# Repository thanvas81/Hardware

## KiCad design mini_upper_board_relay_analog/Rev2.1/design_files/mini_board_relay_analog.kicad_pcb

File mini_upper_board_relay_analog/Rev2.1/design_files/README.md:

# LUX_Project

## Getting started

To make it easy for you to get started with GitLab, here's a list of recommended next steps.

Already a pro? Just edit this README.md and make it your own. Want to make it easy? [Use the template at the bottom](#editing-this-readme)!

## Add your files

- [ ] [Create](https://docs.gitlab.com/ee/user/project/repository/web_editor.html#create-a-file) or [upload](https://docs.gitlab.com/ee/user/project/repository/web_editor.html#upload-a-file) files
- [ ] [Add files using the command line](https://docs.gitlab.com/ee/gitlab-basics/add-file.html#add-a-file-using-the-command-line) or push an existing Git repository with the following command:

```
cd existing_repo
git remote add origin http://192.168.1.53/hardware/boards/lux_project.git
git branch -M main
git push -uf origin main
```

## Integrate with your tools

- [ ] [Set up project integrations](http://192.168.1.53/hardware/boards/lux_project/-/settings/integrations)

## Collaborate with your team

- [ ] [Invite team members and collaborators](https://docs.gitlab.com/ee/user/project/members/)
- [ ] [Create a new merge request](https://docs.gitlab.com/ee/user/project/merge_requests/creating_merge_requests.html)
- [ ] [Automatically close issues from merge requests](https://docs.gitlab.com/ee/user/project/issues/managing_issues.html#closing-issues-automatically)
- [ ] [Enable merge request approvals](https://docs.gitlab.com/ee/user/project/merge_requests/approvals/)
- [ ] [Set auto-merge](https://docs.gitlab.com/ee/user/project/merge_requests/merge_when_pipeline_succeeds.html)

## Test and Deploy

Use the built-in continuous integration in GitLab.

- [ ] [Get started with GitLab CI/CD](https://docs.gitlab.com/ee/ci/quick_start/index.html)
- [ ] [Analyze your code for known vulnerabilities with Static Application Security Testing (SAST)](https://docs.gitlab.com/ee/user/application_security/sast/)
- [ ] [Deploy to Kubernetes, Amazon EC2, or Amazon ECS using Auto Deploy](https://docs.gitlab.com/ee/topics/autodevops/requirements.html)
- [ ] [Use pull-based deployments for improved Kubernetes management](https://docs.gitlab.com/ee/user/clusters/agent/)
- [ ] [Set up protected environments](https://docs.gitlab.com/ee/ci/environments/protected_environments.html)

***

# Editing this README

When you're ready to make this README your own, just edit this file and use the handy template below (or feel free to structure it however you want - this is just a starting point!). Thanks to [makeareadme.com](https://www.makeareadme.com/) for this template.

## Suggestions for a good README

Every project is different, so consider which of these sections apply to yours. The sections used in the template are suggestions for most open source projects. Also keep in mind that while a README can be too long and detailed, too long is better than too short. If you think your README is too long, consider utilizing another form of documentation rather than cutting out information.

## Name
Choose a self-explaining name for your project.

## Description
Let people know what your project can do specifically. Provide context and add a link to any reference visitors might be unfamiliar with. A list of Features or a Background subsection can also be added here. If there are alternatives to your project, this is a good place to list differentiating factors.

## Badges
On some READMEs, you may see small images that convey metadata, such as whether or not all the tests are passing for the project. You can use Shields to add some to your README. Many services also have instructions for adding a badge.

## Visuals
Depending on what you are making, it can be a good idea to include screenshots or even a video (you'll frequently see GIFs rather than actual videos). Tools like ttygif can help, but check out Asciinema for a more sophisticated method.

## Installation
Within a particular ecosystem, there may be a common way of installing things, such as using Yarn, NuGet, or Homebrew. However, consider the possibility that whoever is reading your README is a novice and would like more guidance. Listing specific steps helps remove ambiguity and gets people to using your project as quickly as possible. If it only runs in a specific context like a particular programming language version or operating system or has dependencies that have to be installed manually, also add a Requirements subsection.

## Usage
Use examples liberally, and show the expected output if you can. It's helpful to have inline the smallest example of usage that you can demonstrate, while providing links to more sophisticated examples if they are too long to reasonably include in the README.

## Support
Tell people where they can go to for help. It can be any combination of an issue tracker, a chat room, an email address, etc.

## Roadmap
If you have ideas for releases in the future, it is a good idea to list them in the README.

## Contributing
State if you are open to contributions and what your requirements are for accepting them.

For people who want to make changes to your project, it's helpful to have some documentation on how to get started. Perhaps there is a script that they should run or some environment variables that they need to set. Make these steps explicit. These instructions could also be useful to your future self.

You can also document commands to lint the code or run tests. These steps help to ensure high code quality and reduce the likelihood that the changes inadvertently break something. Having instructions for running tests is especially helpful if it requires external setup, such as starting a Selenium server for testing in a browser.

## Authors and acknowledgment
Show your appreciation to those who have contributed to the project.

## License
For open source projects, say how it is licensed.

## Project status
If you have run out of energy or time for your project, put a note at the top of the README saying that development has slowed down or stopped completely. Someone may choose to fork your project or volunteer to step in as a maintainer or owner, allowing your project to keep going. You can also make an explicit request for maintainers.

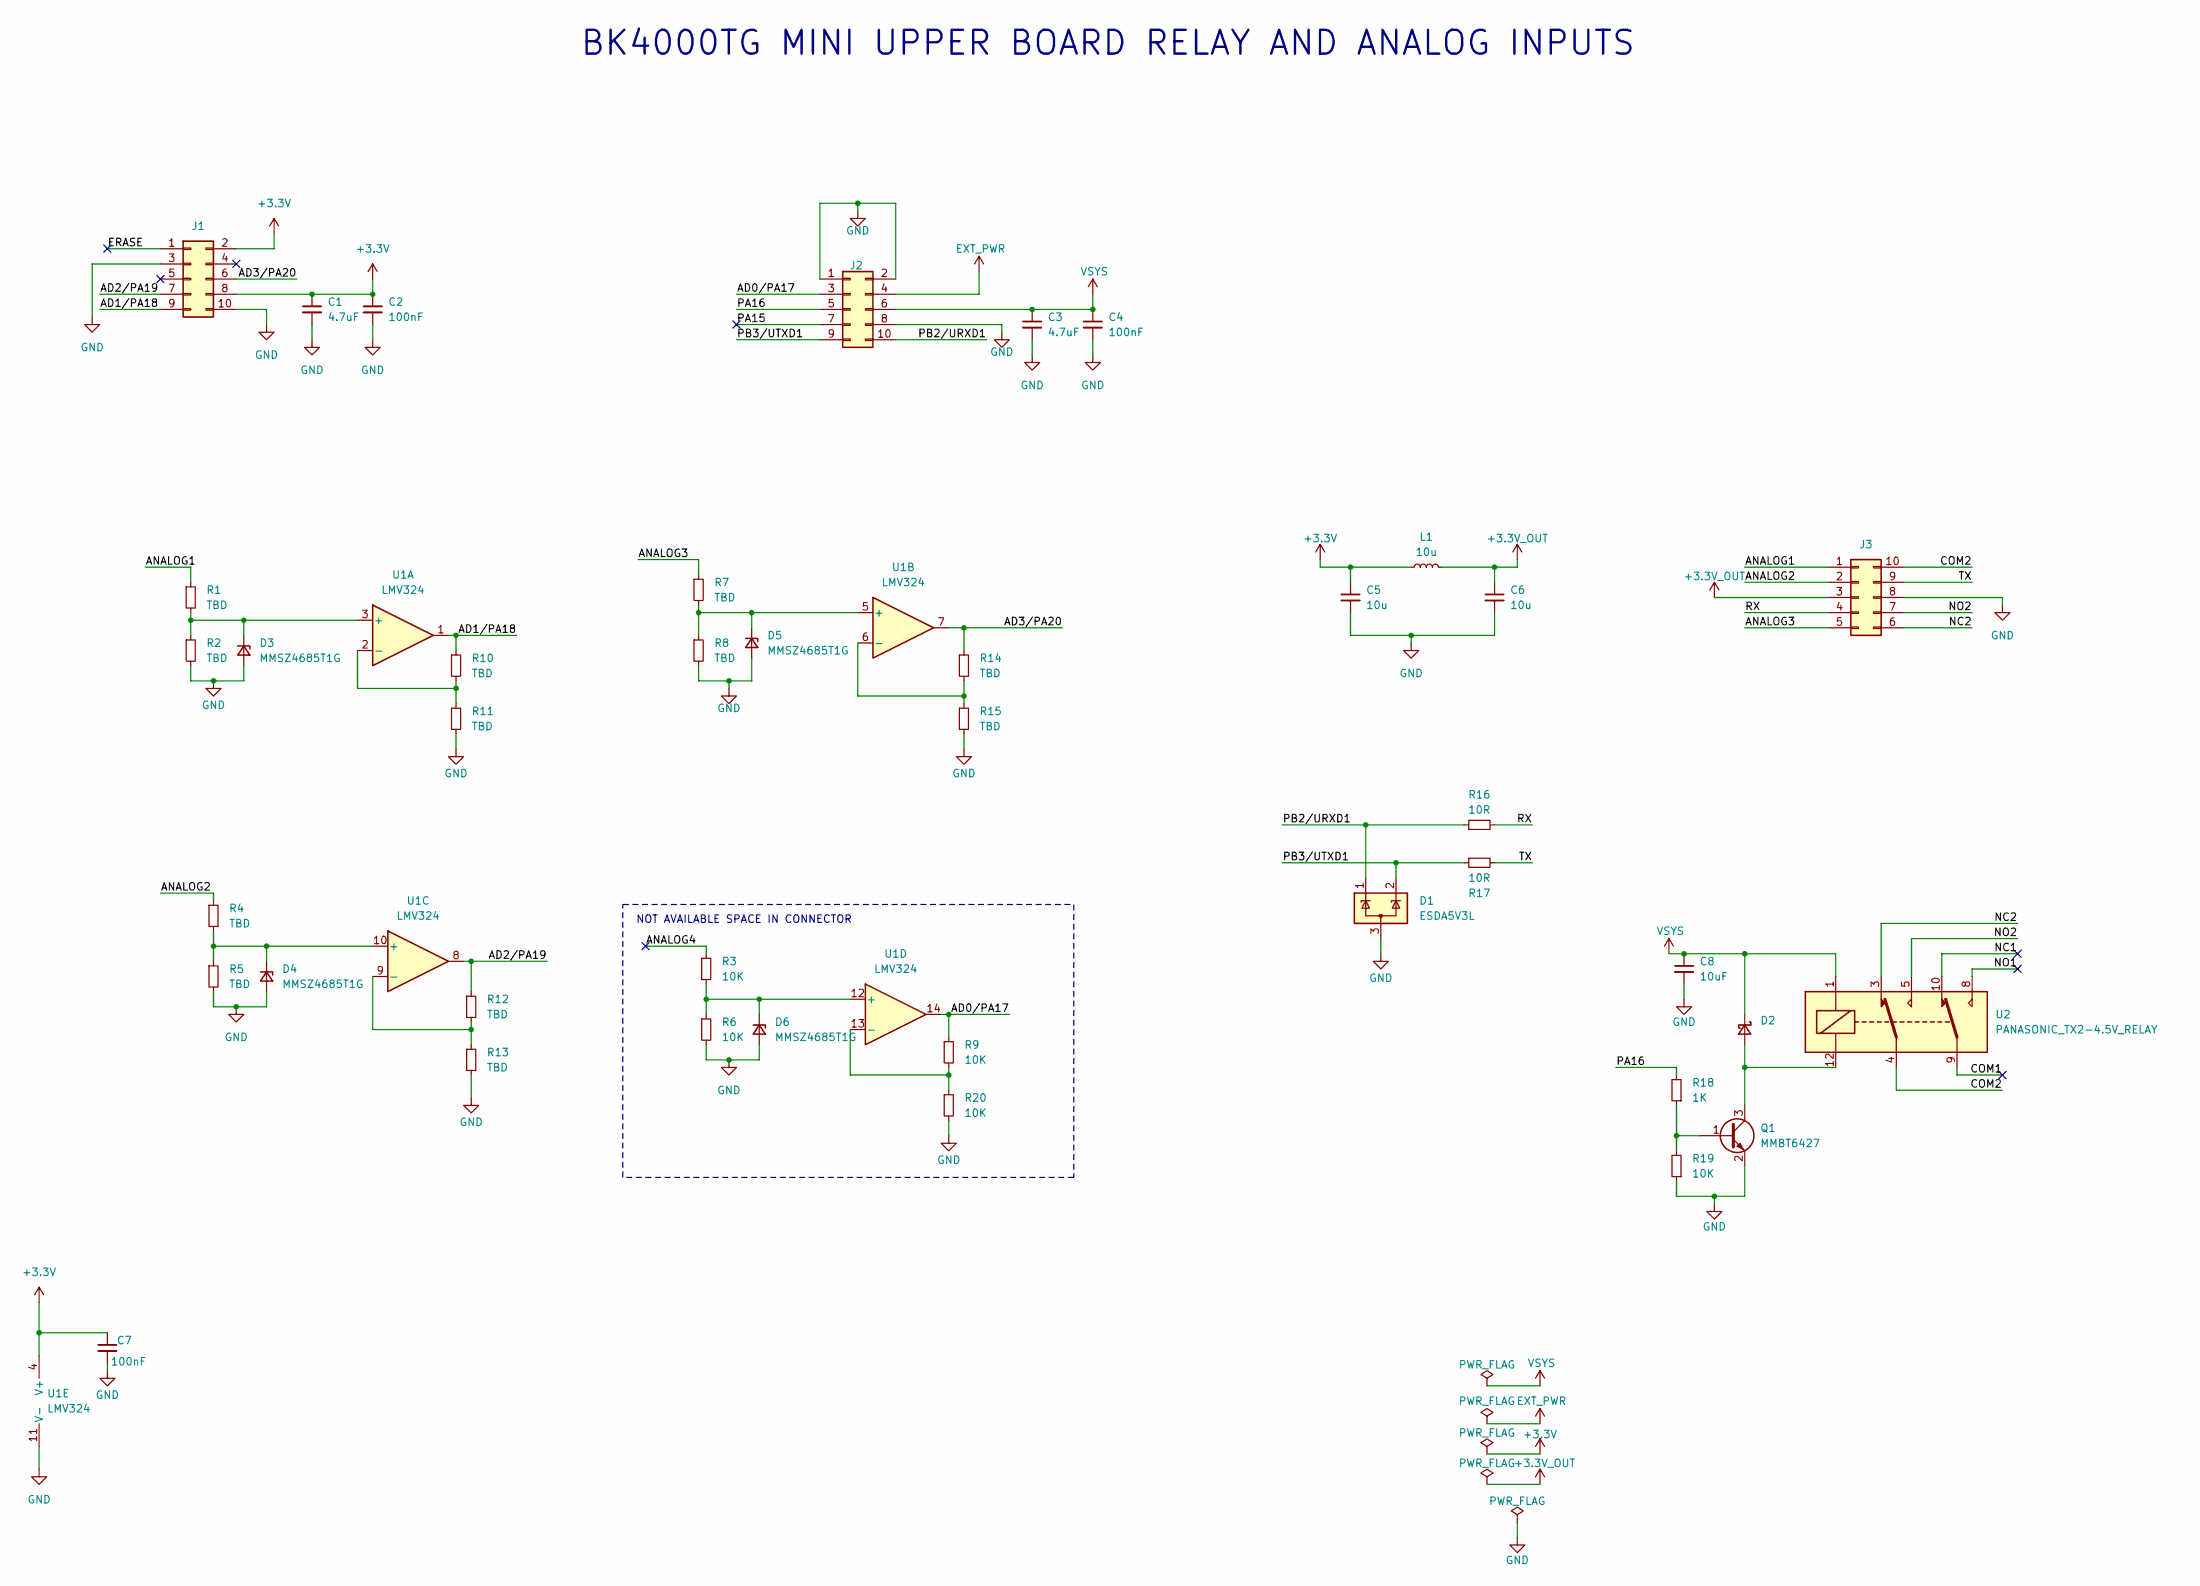
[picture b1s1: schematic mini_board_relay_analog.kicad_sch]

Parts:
C1, C3: 4.7uF; C_0805_2012Metric
C2, C4, C7: 100nF; C_0603_1608Metric
C5, C6: 10u; C_0805_2012Metric
C8: 10uF; C_0805_2012Metric
D1: ESDA5V3L; SOT-23-3
D2: D_Schottky_Small; SOT-23-3
D3, D4, D5, D6: MMSZ4685T1G; D_SOD-123
J1, J2: Header pin 2x5 1.27mm T.H.; PinSocket_2x05_P1.27mm_Vertical
J3: Conn_02x05_Counter_Clockwise; Molex_Mini-Fit_Jr_5569-10A2_2x05_P4.20mm_Horizontal
L1: 10u; L_0805_2012Metric
Q1: MMBT6427; SOT-23
R1, R2, R4, R5, R7, R8, R10, R11, R12, R13, R14, R15: TBD; R_0603_1608Metric
R3, R6, R9, R19, R20: 10K; R_0603_1608Metric
R16, R17: 10R; R_0603_1608Metric
R18: 1K; R_0603_1608Metric
U1: LMV324; TSSOP-14_4.4x5mm_P0.65mm
U2: PANASONIC_TX2-4.5V_RELAY; Relay_DPDT_Panasonic_TX2-4.5V

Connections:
+3.3V: C1.1, C2.1, C5.1, C7.1, J1.2, J1.8, L1.1, U1.4 (V+)
+3.3V_OUT: C6.1, J3.3, L1.2
/AD0/PA17: J2.3, R9.1, U1.14
/AD1/PA18: J1.9, R10.1, U1.1
/AD2/PA19: J1.7, R12.1, U1.8
/AD3/PA20: J1.6, R14.1, U1.7
/ANALOG1: J3.1, R1.1
/ANALOG2: J3.2, R4.1
/ANALOG3: J3.5, R7.1
/ANALOG4: R3.1
/COM1: U2.9
/COM2: J3.10, U2.4
/ERASE: J1.1
/NC1: U2.10
/NC2: J3.6, U2.3
/NO1: U2.8
/NO2: J3.7, U2.5
/PA15: J2.7
/PA16: J2.5, R18.2
/PB2/URXD1: D1.1 (K), J2.10, R16.1
/PB3/UTXD1: D1.2 (K), J2.9, R17.1
/RX: J3.4, R16.2
/TX: J3.9, R17.2
EXT_PWR: J2.4
GND: C1.2, C2.2, C3.2, C4.2, C5.2, C6.2, C7.2, C8.2, D1.3 (A), D3.2 (A), D4.2 (A), D5.2 (A), D6.2 (A), J1.3, J1.10, J2.1, J2.2, J2.8, J3.8, Q1.2 (E), R2.2, R5.2, R6.2, R8.2, R11.2, R13.2, R15.2, R19.1, R20.2, U1.11 (V-)
unnamed: D2.1 (A), Q1.3 (C), U2.12
unnamed: D3.1 (K), R1.2, R2.1, U1.3 (+)
unnamed: D4.1 (K), R4.2, R5.1, U1.10 (+)
unnamed: D5.1 (K), R7.2, R8.1, U1.5 (+)
unnamed: D6.1 (K), R3.2, R6.1, U1.12 (+)
unnamed: Q1.1 (B), R18.1, R19.2
unnamed: R10.2, R11.1, U1.2 (-)
unnamed: R14.2, R15.1, U1.6 (-)
unnamed: R12.2, R13.1, U1.9 (-)
unnamed: R9.2, R20.1, U1.13 (-)
VSYS: C3.1, C4.1, C8.1, D2.3 (K), J2.6, U2.1

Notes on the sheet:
NOT AVAILABLE SPACE IN CONNECTOR
BK4000TG MINI UPPER BOARD RELAY AND ANALOG INPUTS

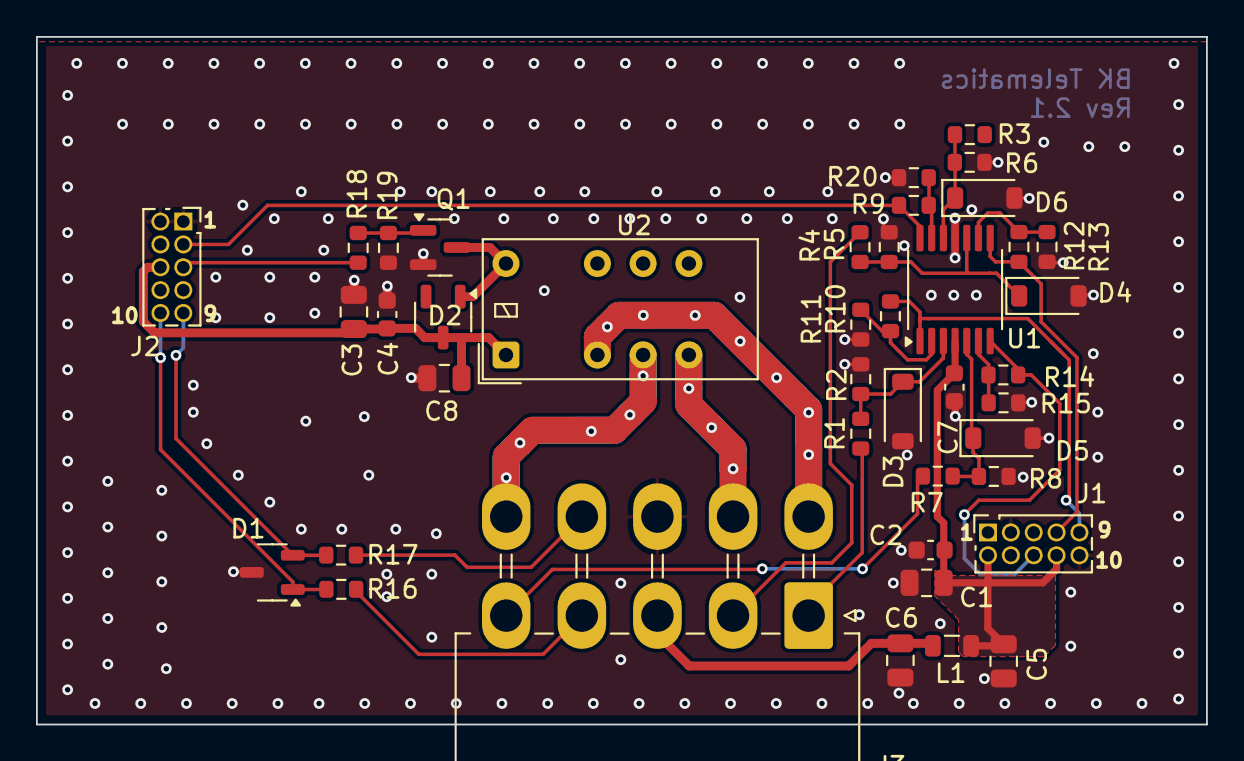
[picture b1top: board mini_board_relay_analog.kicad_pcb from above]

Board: 2 copper layers, 65.0 x 38.2 mm, 41 parts (0 on the bottom side), 29 nets.

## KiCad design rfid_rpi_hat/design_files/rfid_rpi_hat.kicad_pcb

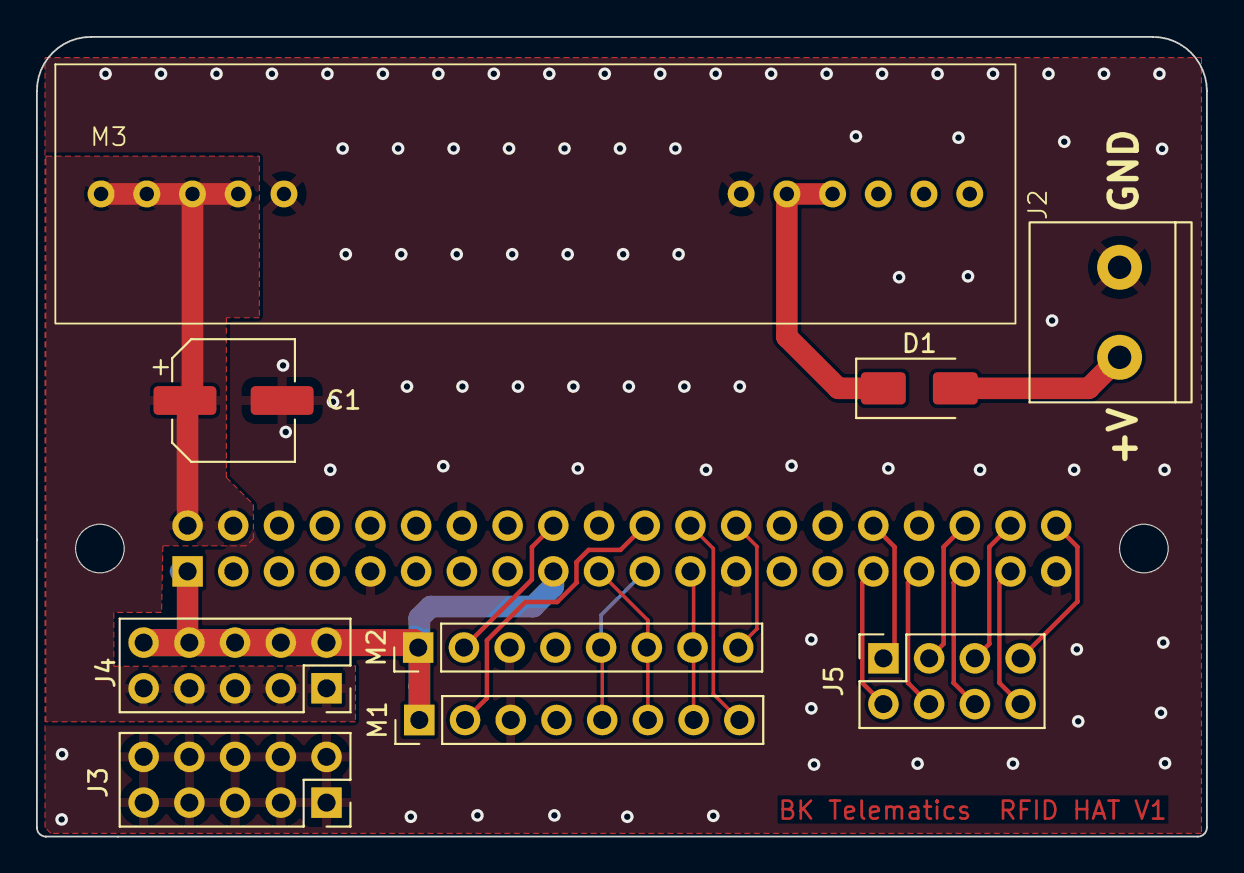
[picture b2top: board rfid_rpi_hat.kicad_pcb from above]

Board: 2 copper layers, 65.0 x 44.4 mm, 12 parts (1 on the bottom side), 20 nets.

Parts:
C1: 100uF; CP_Elec_6.3x7.7
D1: D_Small_Filled; D_SMA
J1: Conn_02x20_Odd_Even; PinSocket_2x20_P2.54mm_Vertical
J2: Screw_Terminal_01x02; Conn_CUI_TB003-500-P02BE
J3, J4: Conn_02x05_Odd_Even; PinSocket_2x05_P2.54mm_Vertical
J5: Conn_02x04_Counter_Clockwise; PinSocket_2x04_P2.54mm_Vertical
M1, M2: PinHeader_1x08_P2.54mm_Vertical
M3: MeanWell_NID35-5
MH1, MH2: MountingHole_2.7mm_M2.5

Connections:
+3V3: J1.1, J1.17, J4.2, J4.4, J4.6, J4.8, J4.10, M1.1 (VCC), M2.1 (VCC)
+5V: C1.1, J1.2, J1.4, J4.1, J4.3, J4.5, J4.7, J4.9, M3.1 (VOUT), M3.2 (VOUT), M3.3 (VOUT), M3.4 (VOUT)
/GPIO6: J1.31, J5.2
/GPIO7/SPI0.CE1: J1.26, M2.8 (SS)
/GPIO8/SPI0.CE0: J1.24, M1.8 (SS)
/GPIO9/SPI0.MISO: J1.21, M1.5 (MISO), M2.5 (MISO)
/GPIO10/SPI0.MOSI: J1.19, M1.6 (MOSI), M2.6 (MOSI)
/GPIO11/SPI0.SCLK: J1.23, M1.7 (SCK), M2.7 (SCK)
/GPIO12/PWM0: J1.32, J5.1
/GPIO13/PWM1: J1.33, J5.4
/GPIO16: J1.36, J5.3
/GPIO19/PCM.FS: J1.35, J5.6
/GPIO20/PCM.DIN: J1.38, J5.5
/GPIO21/PCM.DOUT: J1.40, J5.7
/GPIO24: J1.18, M2.2 (RST)
/GPIO25: J1.22, M1.2 (RST)
/GPIO26: J1.37, J5.8
GND: C1.2, J1.6, J1.9, J1.14, J1.20, J1.25, J1.30, J1.34, J1.39, J2.2, J3.1, J3.2, J3.3, J3.4, J3.5, J3.6, J3.7, J3.8, J3.9, J3.10, M1.3 (GND), M2.3 (GND), M3.5 (COM), M3.6 (COM)
unnamed: D1.2 (A), J2.1
unnamed: D1.1 (K), M3.7 (VIN), M3.8 (VIN)

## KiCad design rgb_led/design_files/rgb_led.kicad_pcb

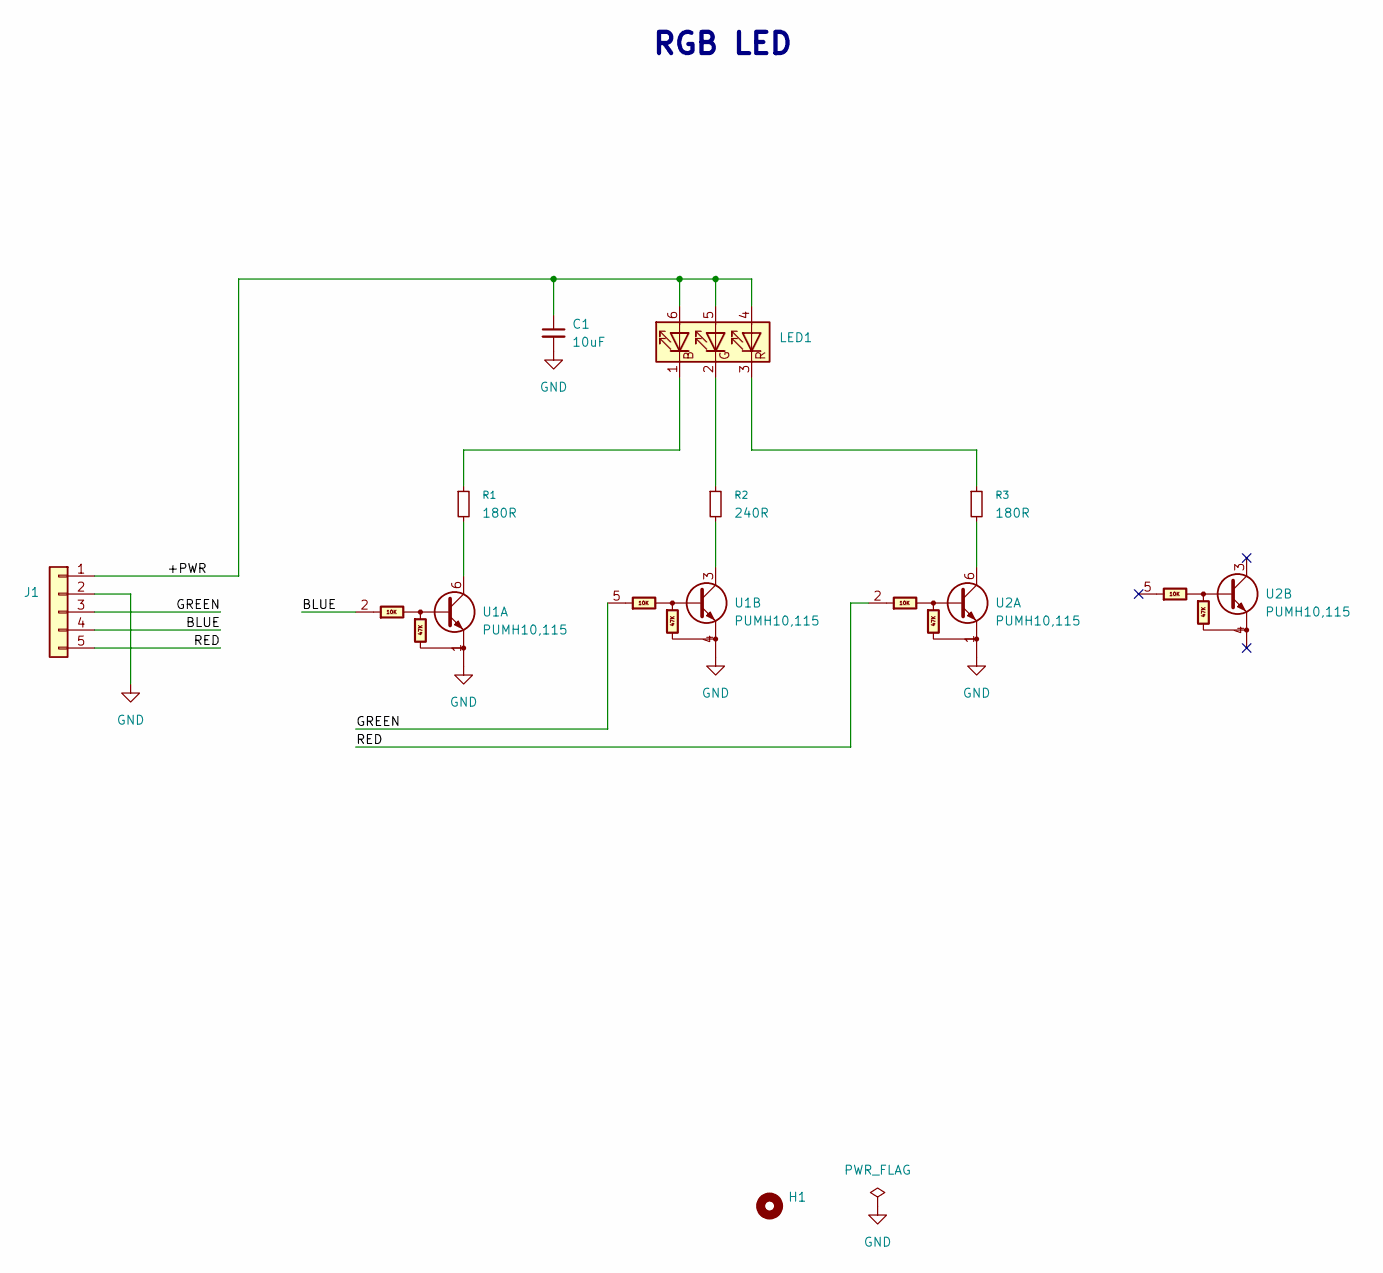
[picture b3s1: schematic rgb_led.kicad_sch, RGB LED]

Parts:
C1: 10uF; C_0805_2012Metric
H1: MountingHole; MountingHole_3.2mm_M3
J1: Conn_01x05; JST_ZH_B5B-ZR_1x05_P1.50mm_Vertical
LED1: CLX6F-FKC-CKNNQDGBB7A363
R1, R3: 180R; R_0805_2012Metric
R2: 240R; R_0805_2012Metric
U1, U2: PUMH10,115; SOT-363_SC-70-6

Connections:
/+PWR: C1.1, J1.1, LED1.4 (BA), LED1.5 (GA), LED1.6 (RA)
/BLUE: J1.4, U1.2
/GREEN: J1.3, U1.5
/RED: J1.5, U2.2
GND: C1.2, J1.2, U1.1, U1.4, U2.1
unnamed: LED1.3 (BK), R3.1
unnamed: LED1.2 (GK), R2.1
unnamed: LED1.1 (RK), R1.1
unnamed: R1.2, U1.6
unnamed: R2.2, U1.3
unnamed: R3.2, U2.6

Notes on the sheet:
RGB LED

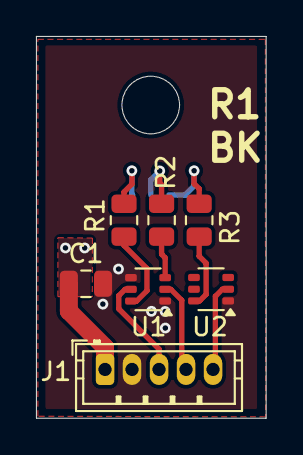
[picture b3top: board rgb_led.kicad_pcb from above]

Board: 2 copper layers, 12.8 x 21.2 mm, 9 parts (1 on the bottom side), 11 nets.

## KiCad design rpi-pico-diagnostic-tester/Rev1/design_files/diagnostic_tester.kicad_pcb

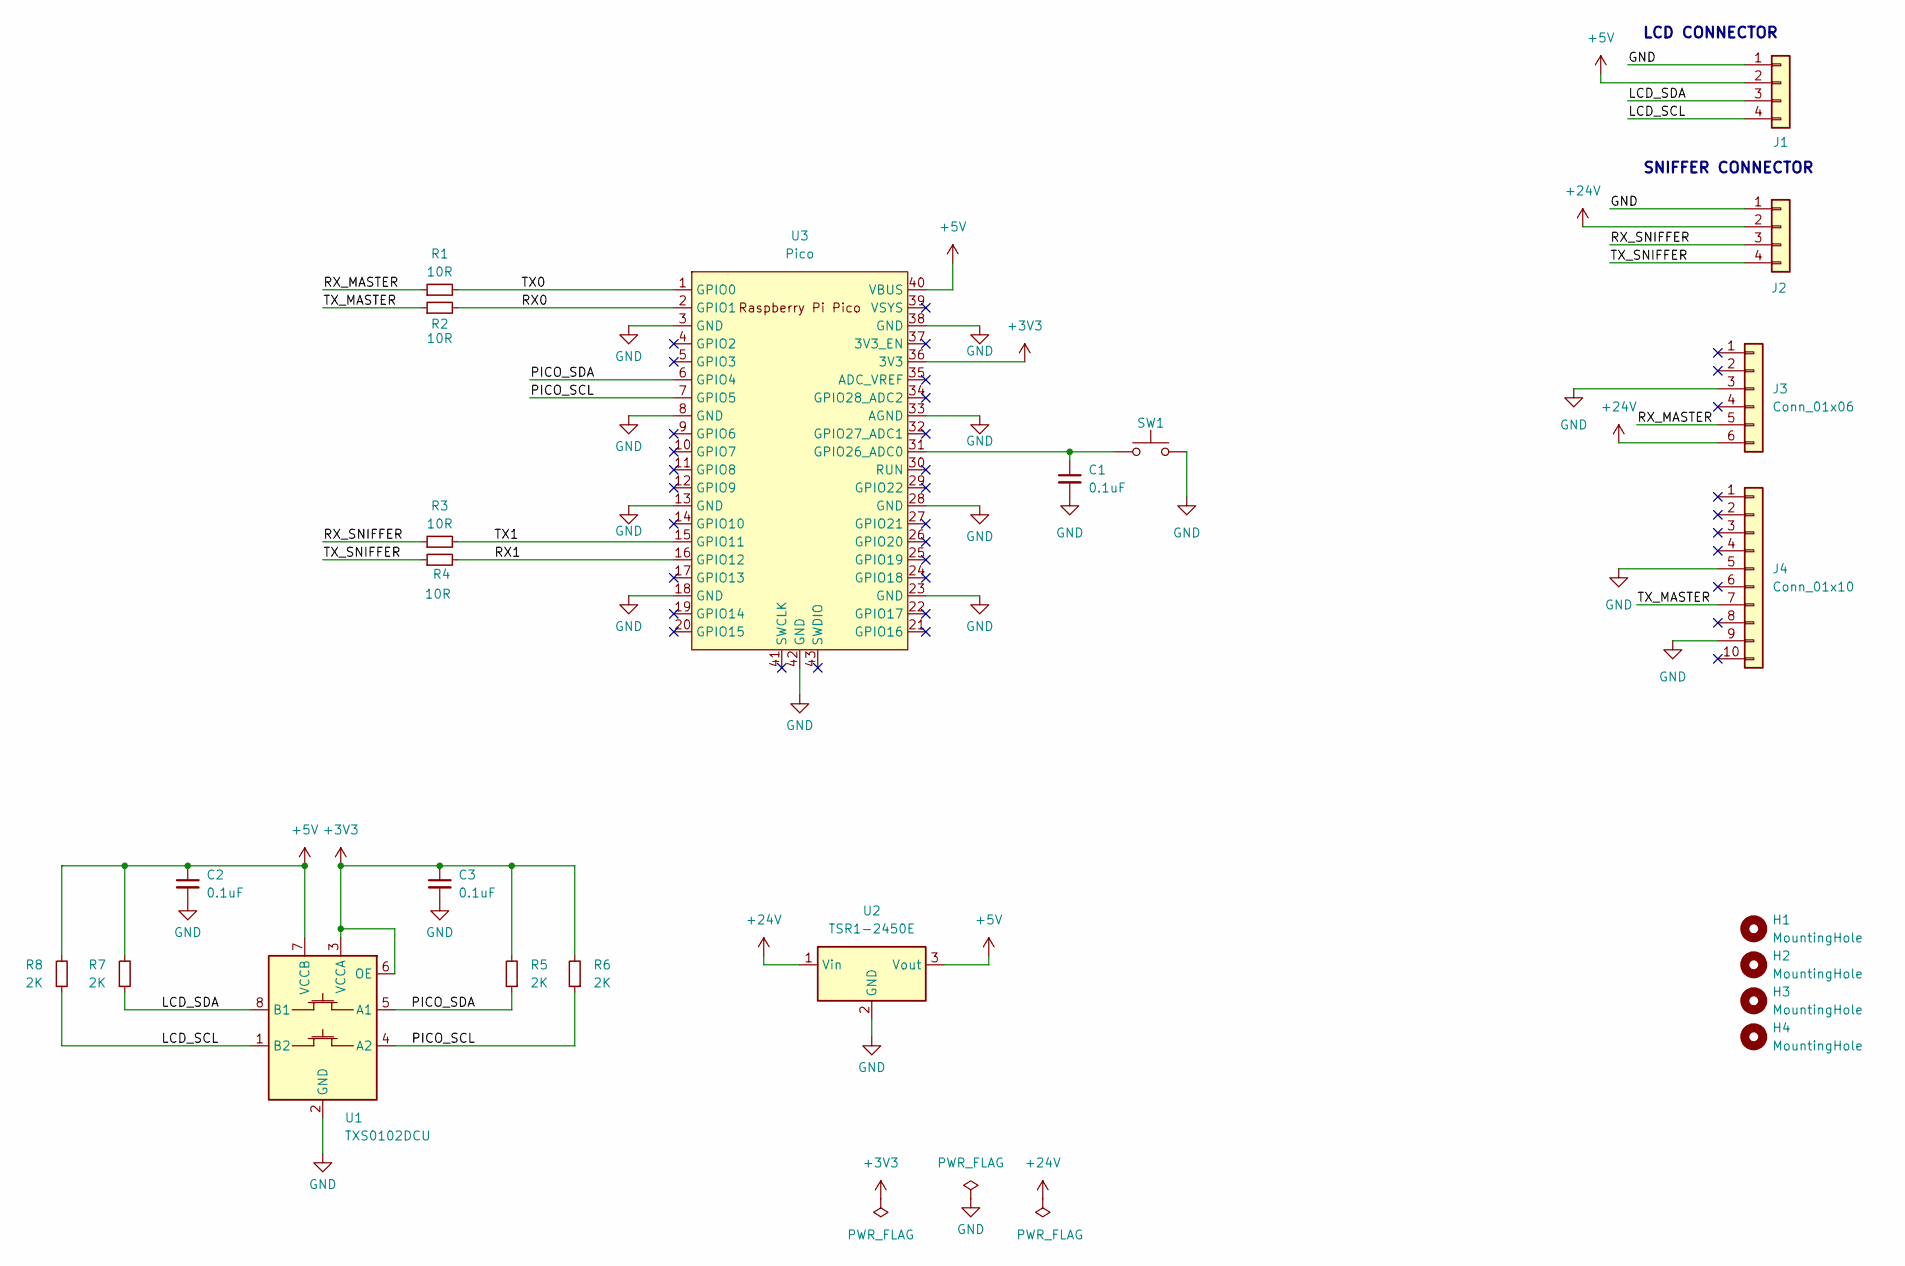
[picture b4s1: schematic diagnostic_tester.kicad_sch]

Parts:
C1, C2, C3: 0.1uF; C_0603_1608Metric
H1, H2, H3, H4: MountingHole; MountingHole_3.2mm_M3_ISO14580
J1, J2: Conn_01x04; PinHeader_1x04_P2.54mm_Vertical
J3: Conn_01x06; Molex_Mini-Fit_Jr_5569-06A2_2x03_P4.20mm_Horizontal
J4: Conn_01x10; Molex_Mini-Fit_Jr_5569-10A2_2x05_P4.20mm_Horizontal
R1, R2, R3, R4: 10R; R_0603_1608Metric
R5, R6, R7, R8: 2K; R_0603_1608Metric
SW1: FSM14JLH; SW_PUSH_6mm_H9.5mm
U1: TXS0102DCU; Package_SO_VSSOP-8_P0.5mm
U2: TSR1-2450E; Converter_DCDC_TRACO_TSR1-xxxxE_THT
U3: Pico; RPi_Pico_SMD_TH

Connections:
+3V3: C3.1, R5.2, R6.2, U1.3 (VCCA), U1.6 (OE), U3.36 (3V3)
+5V: C2.1, J1.2, R7.2, R8.2, U1.7 (VCCB), U2.3 (Vout), U3.40 (VBUS)
+24V: J2.2, J3.6, U2.1 (Vin)
/LCD_SCL: J1.4, R8.1, U1.1 (B2)
/LCD_SDA: J1.3, R7.1, U1.8 (B1)
/PICO_SCL: R6.1, U1.4 (A2), U3.7 (GPIO5)
/PICO_SDA: R5.1, U1.5 (A1), U3.6 (GPIO4)
/RX0: R2.2, U3.2 (GPIO1)
/RX1: R4.2, U3.16 (GPIO12)
/RX_MASTER: J3.5, R1.1
/RX_SNIFFER: J2.3, R3.1
/TX0: R1.2, U3.1 (GPIO0)
/TX1: R3.2, U3.15 (GPIO11)
/TX_MASTER: J4.7, R2.1
/TX_SNIFFER: J2.4, R4.1
GND: C1.2, C2.2, C3.2, J1.1, J2.1, J3.3, J4.5, J4.9, SW1.2, U1.2 (GND), U2.2 (GND), U3.3 (GND), U3.8 (GND), U3.13 (GND), U3.18 (GND), U3.23 (GND), U3.28 (GND), U3.33 (AGND), U3.38 (GND), U3.42 (GND)
unnamed: C1.1, SW1.1, U3.31 (GPIO26_ADC0)

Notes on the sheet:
SNIFFER CONNECTOR
LCD CONNECTOR

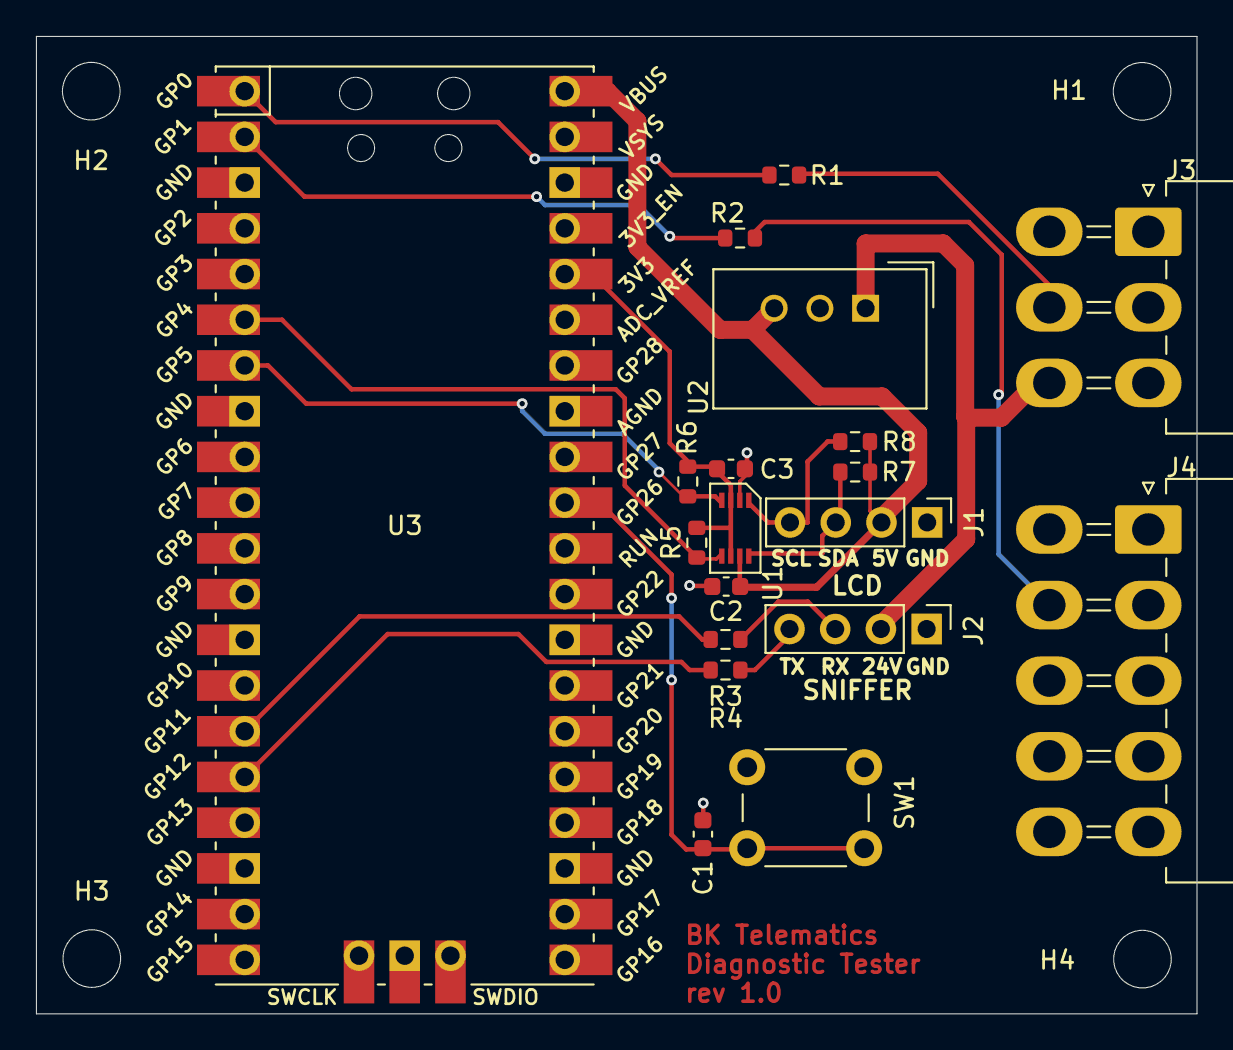
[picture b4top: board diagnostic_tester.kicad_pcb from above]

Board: 2 copper layers, 64.5 x 54.3 mm, 23 parts (0 on the bottom side), 17 nets.

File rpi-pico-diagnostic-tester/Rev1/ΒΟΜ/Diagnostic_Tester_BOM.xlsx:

Description | Designator | Footprint | Quantity | Value
Resistor | R1,R2,R3,R4 | 0603 | 4 | 10 Ω
Resistor | R5,R6,R7,R8 | 0603 | 4 | 2K Ω
Capacitor | C1,C2,C3 | 0603 | 3 | 0,1uF
TSR1-2450E | U2 |  | 1
PS33BBK | SW1 |  | 1

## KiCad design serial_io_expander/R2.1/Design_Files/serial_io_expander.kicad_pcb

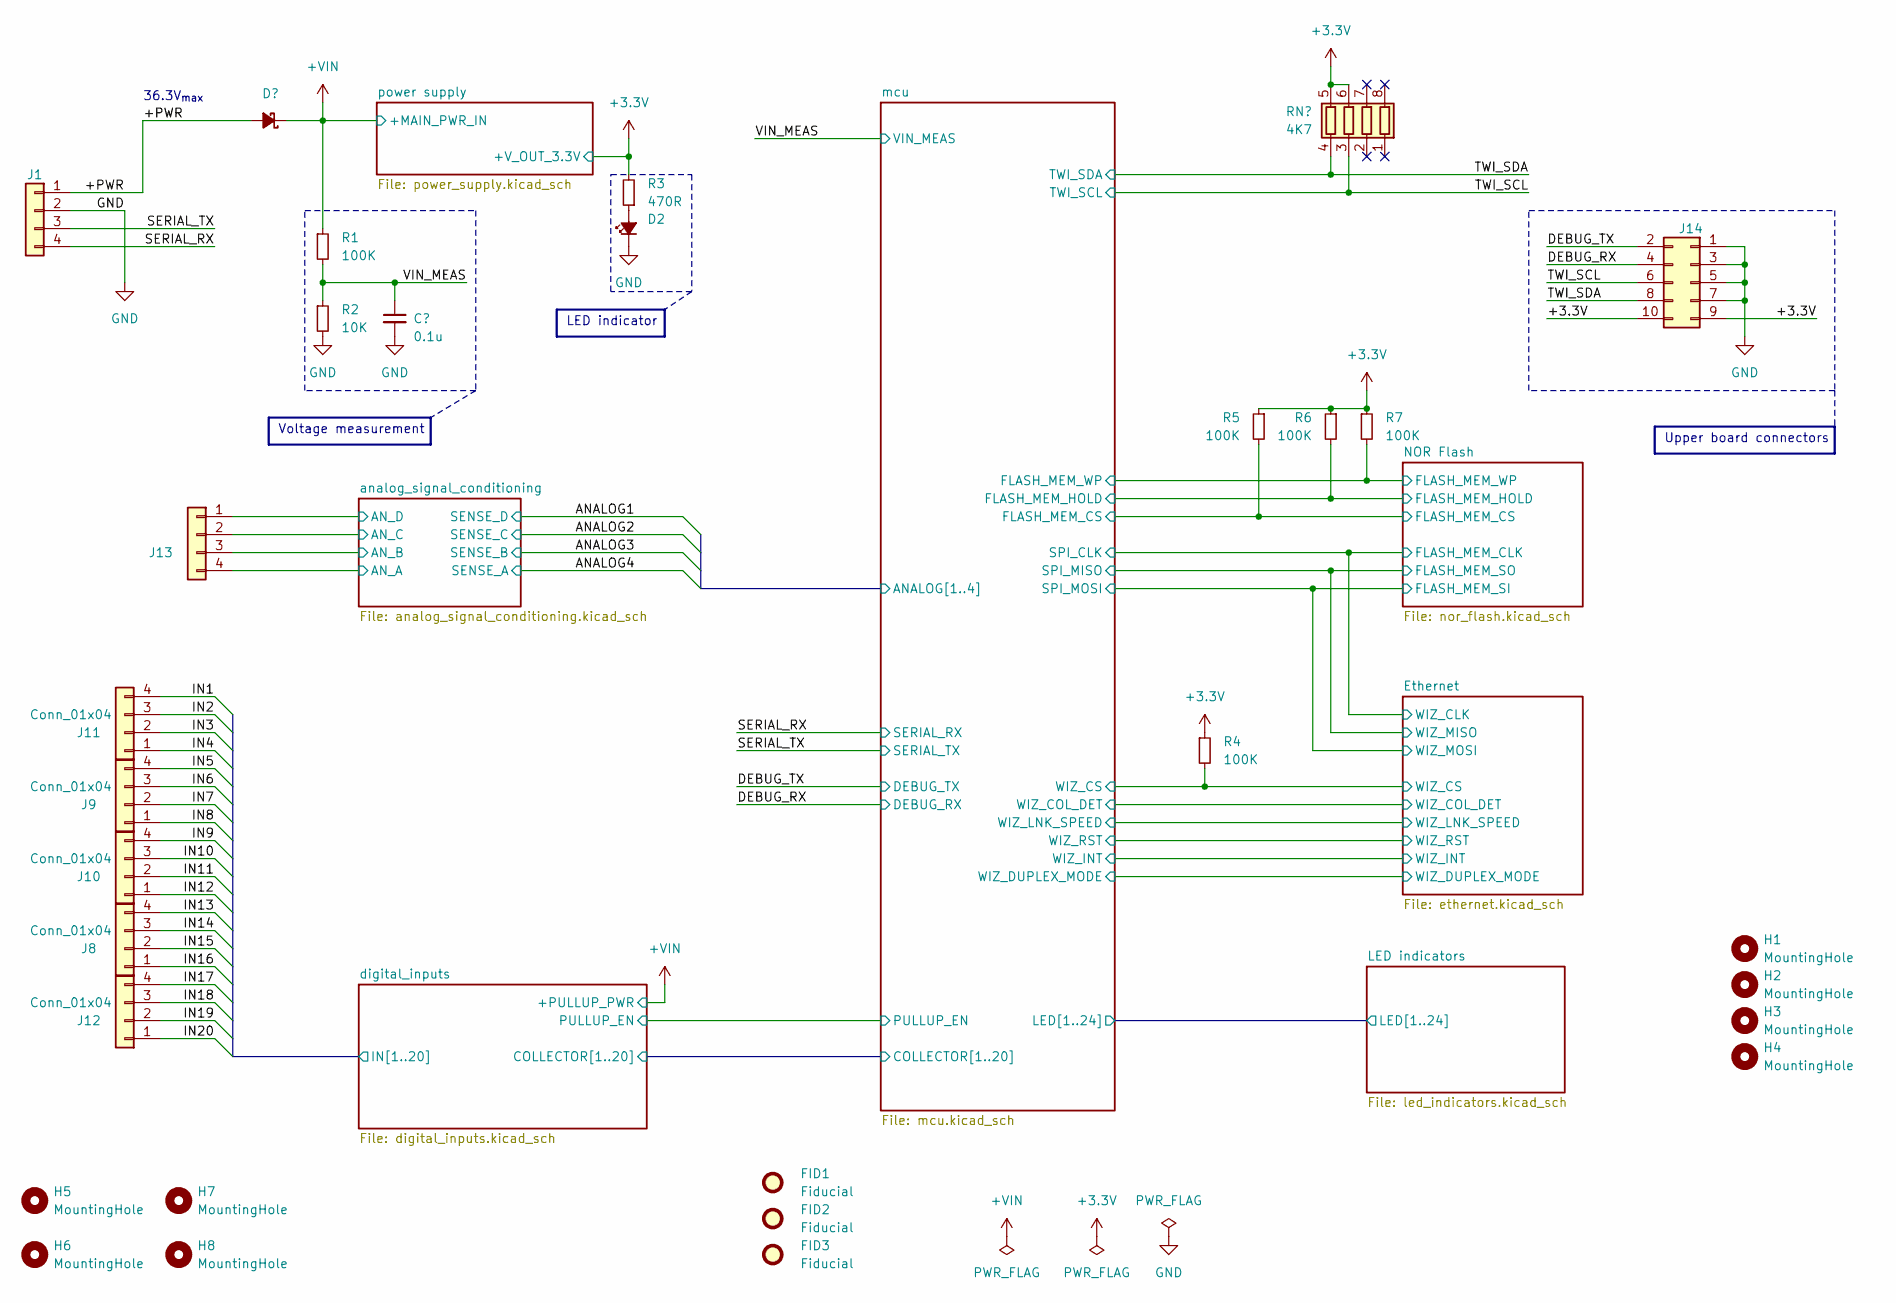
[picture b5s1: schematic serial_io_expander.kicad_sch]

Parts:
C1: 0.1u; C_0603_1608Metric; PartkeeprID 50
D1: SBR3U60P1Q-7; D_PowerDI-123; PartkeeprID 43
D2: LED_Small_Filled; LED_0603_1608Metric
FID1, FID2, FID3: Fiducial; Fiducial_1mm_Mask2mm
H1, H2, H3, H4: MountingHole; MountingHole_4.3mm_M4
H5, H6, H7, H8: MountingHole; MountingHole_3.2mm_M3_DIN965
J1, J8, J9, J10, J11, J12, J13: Conn_01x04; TerminalBlock_IMO_203001M-4
J14: PinHeader_2x05_P2.54mm_Vertical
R1, R4, R5, R6, R7: 100K; R_0603_1608Metric
R2: 10K; R_0603_1608Metric
R3: 470R; R_0603_1608Metric
RN1: 4K7; R_Array_Concave_4x0603

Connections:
+VIN: D1.1 (K), R1.1; also elsewhere on the board
/+PWR: D1.2 (A), J1.1
/DEBUG_RX: J14.4; also elsewhere on the board
/DEBUG_TX: J14.2; also elsewhere on the board
/Ethernet/WIZ_CS: R4.2; also elsewhere on the board
/NOR Flash/FLASH_MEM_CS: R5.2; also elsewhere on the board
/NOR Flash/FLASH_MEM_HOLD: R6.2; also elsewhere on the board
/NOR Flash/FLASH_MEM_WP: R7.2; also elsewhere on the board
/SERIAL_RX: J1.4; also elsewhere on the board
/SERIAL_TX: J1.3; also elsewhere on the board
/VIN_MEAS: C1.1, R1.2, R2.1; also elsewhere on the board
/analog_signal_conditioning/AN_A: J13.4; also elsewhere on the board
/analog_signal_conditioning/AN_B: J13.3; also elsewhere on the board
/analog_signal_conditioning/AN_C: J13.2; also elsewhere on the board
/analog_signal_conditioning/AN_D: J13.1; also elsewhere on the board
/digital_inputs/IN1: J11.4; also elsewhere on the board
/digital_inputs/IN2: J11.3; also elsewhere on the board
/digital_inputs/IN3: J11.2; also elsewhere on the board
/digital_inputs/IN4: J11.1; also elsewhere on the board
/digital_inputs/IN5: J9.4; also elsewhere on the board
/digital_inputs/IN6: J9.3; also elsewhere on the board
/digital_inputs/IN7: J9.2; also elsewhere on the board
/digital_inputs/IN8: J9.1; also elsewhere on the board
/digital_inputs/IN9: J10.4; also elsewhere on the board
/digital_inputs/IN10: J10.3; also elsewhere on the board
/digital_inputs/IN11: J10.2; also elsewhere on the board
/digital_inputs/IN12: J10.1; also elsewhere on the board
/digital_inputs/IN13: J8.4; also elsewhere on the board
/digital_inputs/IN14: J8.3; also elsewhere on the board
/digital_inputs/IN15: J8.2; also elsewhere on the board
/digital_inputs/IN16: J8.1; also elsewhere on the board
/digital_inputs/IN17: J12.4; also elsewhere on the board
/digital_inputs/IN18: J12.3; also elsewhere on the board
/digital_inputs/IN19: J12.2; also elsewhere on the board
/digital_inputs/IN20: J12.1; also elsewhere on the board
GND: C1.2, D2.1 (K), J1.2, J14.1, J14.3, J14.5, J14.7, R2.2; also elsewhere on the board
unnamed: D2.2 (A), R3.1

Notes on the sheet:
36.3V_{max}
Voltage measurement
Upper board connectors
LED indicator

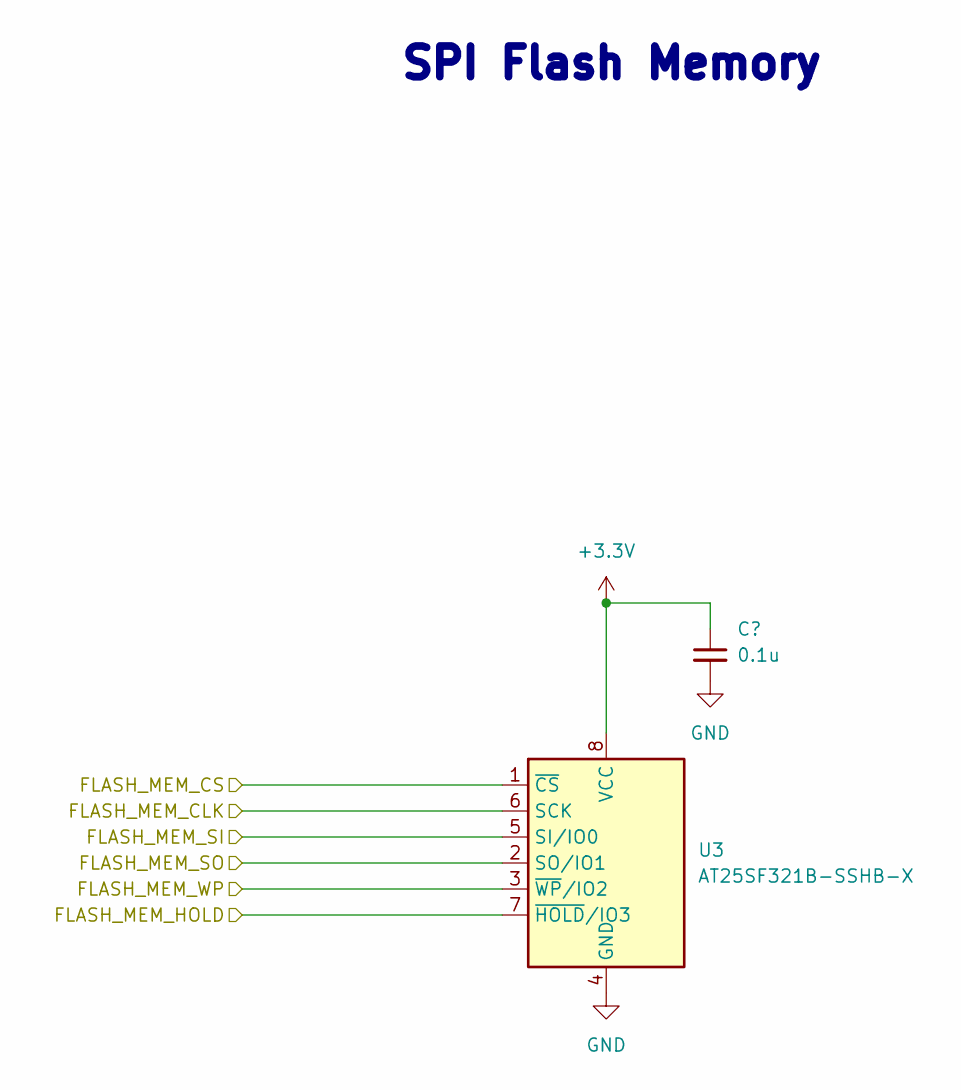
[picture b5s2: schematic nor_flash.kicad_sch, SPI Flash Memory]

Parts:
C12: 0.1u; C_0603_1608Metric; PartkeeprID 50
U3: AT25SF321B-SSHB-X; SOIC-8_3.9x4.9mm_P1.27mm

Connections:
/Ethernet/WIZ_CLK: U3.6 (SCK); also elsewhere on the board
/Ethernet/WIZ_MISO: U3.2 (SO/IO1); also elsewhere on the board
/Ethernet/WIZ_MOSI: U3.5 (SI/IO0); also elsewhere on the board
/NOR Flash/FLASH_MEM_CS: U3.1 (~CS); also elsewhere on the board
/NOR Flash/FLASH_MEM_HOLD: U3.7 (~HOLD/IO3); also elsewhere on the board
/NOR Flash/FLASH_MEM_WP: U3.3 (~WP/IO2); also elsewhere on the board
GND: C12.2, U3.4 (GND); also elsewhere on the board

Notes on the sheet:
${TITLE}
